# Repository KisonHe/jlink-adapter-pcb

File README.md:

# jlink-adapter-pcb

[bom](http://htmlpreview.github.io/?https://github.com/KisonHe/jlink-adapter-pcb/blob/master/jlink-adapter/bom/ibom.html)

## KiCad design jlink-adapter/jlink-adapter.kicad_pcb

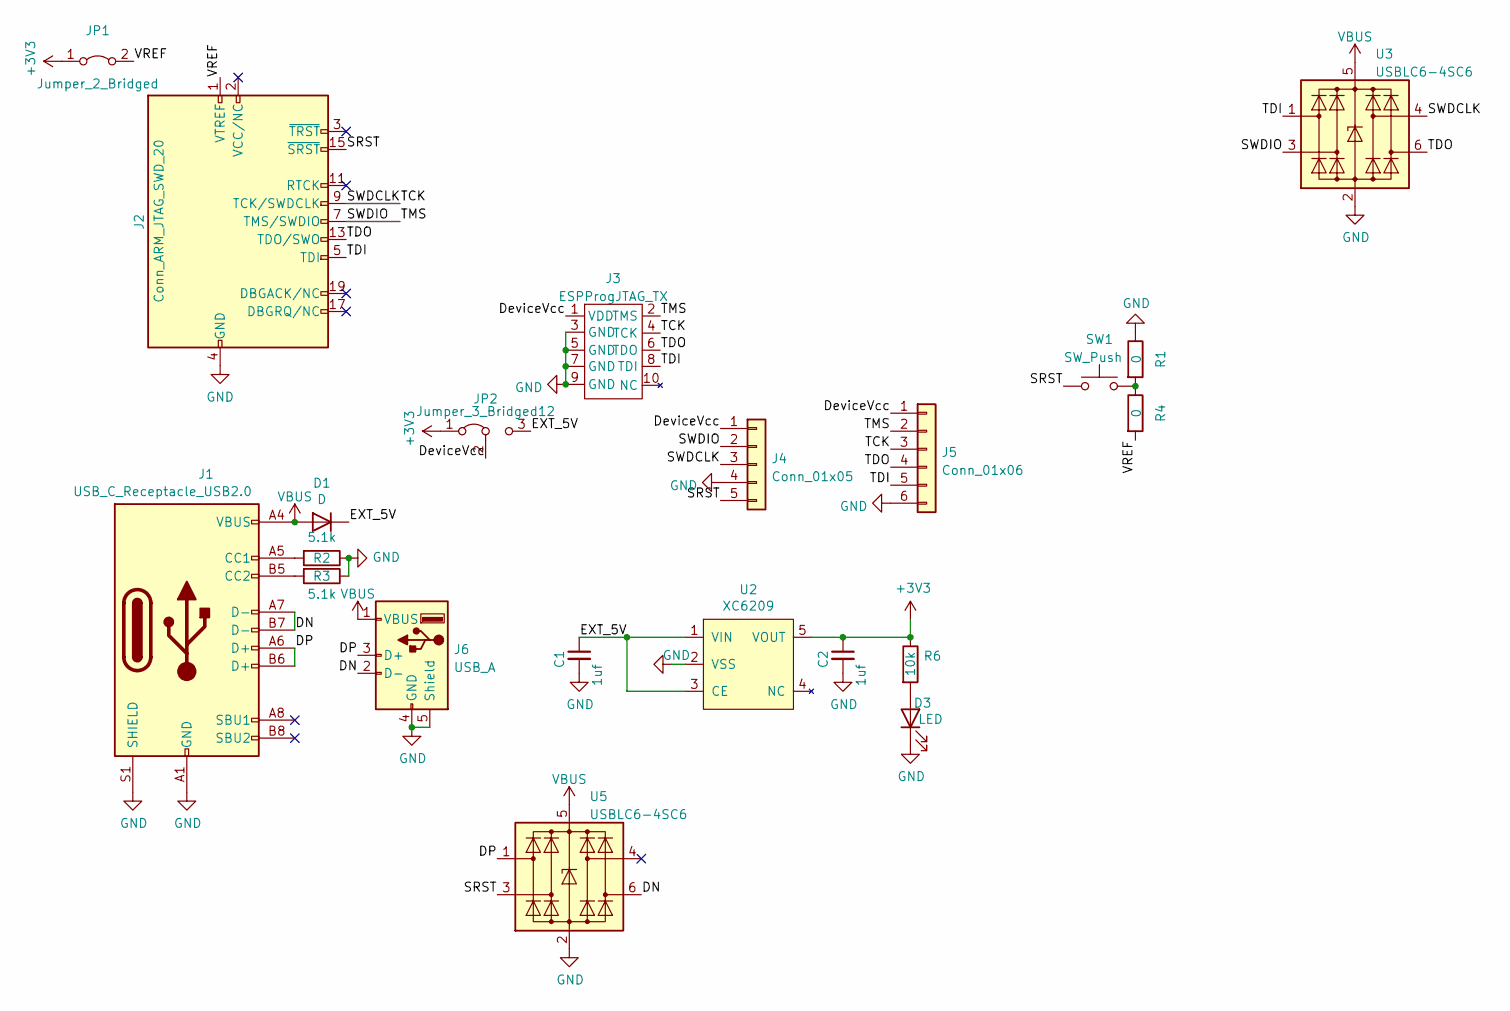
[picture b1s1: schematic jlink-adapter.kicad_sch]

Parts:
C1, C2: 1uf; C_0603_1608Metric
D1: D; C8678; LCSC C8678
D3: LED; LED_0603_1608Metric; LCSC C181863
J1: USB_C_Receptacle_USB2.0; USB_C_Receptacle_HRO_TYPE-C-31-M-12; LCSC C165948
J2: Conn_ARM_JTAG_SWD_20; PinHeader_2x10_P2.54mm_Vertical
J3: ESPProgJTAG_TX; IDC_1.27mm_10P
J4: Conn_01x05; PinHeader_1x05_P2.54mm_Vertical
J5: Conn_01x06; PinHeader_1x06_P2.54mm_Vertical
J6: USB_A; USB_A_CONNFLY_DS1095-WNR0; LCSC C2345
JP1: Jumper_2_Bridged; PinHeader_1x02_P2.54mm_Vertical; LCSC 6209
JP2: Jumper_3_Bridged12; PinHeader_1x03_P2.54mm_Vertical
R1, R4: 0; R_0603_1608Metric; LCSC C325524
R2, R3: 5.1k; R_0603_1608Metric; LCSC C325524
R6: 10k; R_0603_1608Metric
SW1: SW_Push; SW_SPST_CK_RS282G05A3
U2: XC6209; SOT-23-5; LCSC C216624
U3, U5: USBLC6-4SC6; SOT-23-6

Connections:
+3V3: C2.1, JP1.1 (A), JP2.1 (A), R6.1, U2.5 (VOUT)
/DN: J1.A7 (D-), J1.B7 (D-), J6.2 (D-), U5.6 (I/O4)
/DP: J1.A6 (D+), J1.B6 (D+), J6.3 (D+), U5.1 (I/O1)
/DeviceVcc: J3.1 (VDD), J4.1, J5.1, JP2.2 (C)
/EXT_5V: C1.1, D1.1 (K), JP2.3 (B), U2.1 (VIN), U2.3 (CE)
/SRST: J2.15 (~SRST), J4.5, SW1.1, U5.3 (I/O2)
/SWDCLK: J2.9 (TCK/SWDCLK), J3.4 (TCK), J4.3, J5.3, U3.4 (I/O3)
/SWDIO: J2.7 (TMS/SWDIO), J3.2 (TMS), J4.2, J5.2, U3.3 (I/O2)
/TDI: J2.5 (TDI), J3.8 (TDI), J5.5, U3.1 (I/O1)
/TDO: J2.13 (TDO/SWO), J3.6 (TDO), J5.4, U3.6 (I/O4)
/VREF: J2.1 (VTREF), JP1.2 (B), R4.2
GND: C1.2, C2.2, D3.1 (K), J1.A1 (GND), J1.A12 (GND), J1.B1 (GND), J1.B12 (GND), J1.S1 (SHIELD), J2.4 (GND), J2.6 (GND), J2.8 (GND), J2.10 (GND), J2.12 (GND), J2.14 (GND), J2.16 (GND), J2.18 (GND), J2.20 (GND), J3.3 (GND), J3.5 (GND), J3.7 (GND), J3.9 (GND), J4.4, J5.6, J6.4 (GND), J6.5 (Shield), R1.1, R2.1, R3.1, U2.2 (VSS), U3.2 (GND), U5.2 (GND)
unnamed: D3.2 (A), R6.2
unnamed: J1.A5 (CC1), R2.2
unnamed: J1.B5 (CC2), R3.2
unnamed: R1.2, R4.1, SW1.2
VBUS: D1.2 (A), J1.A4 (VBUS), J1.A9 (VBUS), J1.B4 (VBUS), J1.B9 (VBUS), J6.1 (VBUS), U3.5 (VBUS), U5.5 (VBUS)

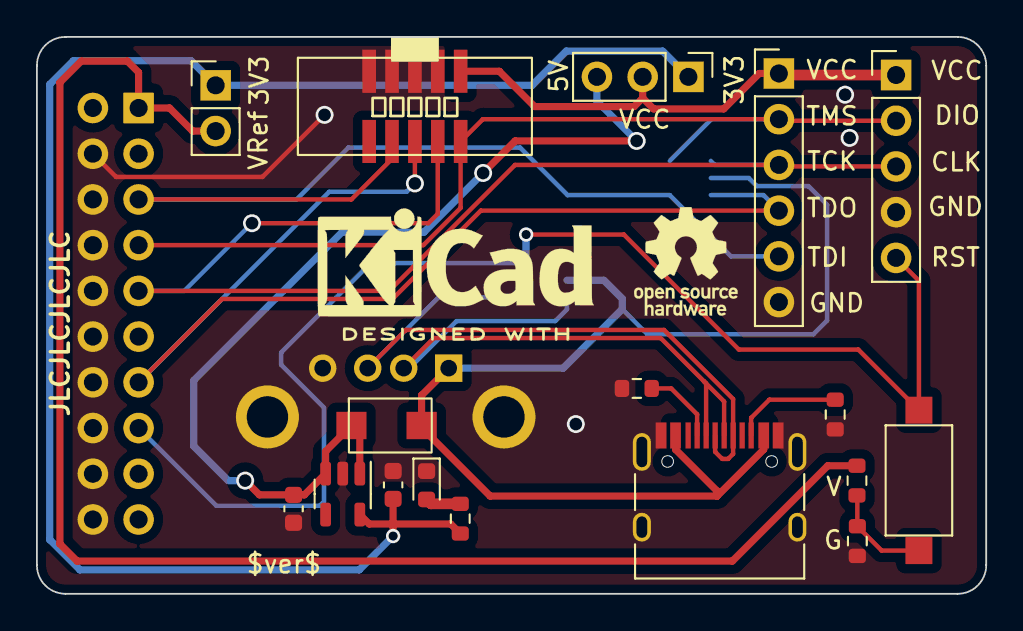
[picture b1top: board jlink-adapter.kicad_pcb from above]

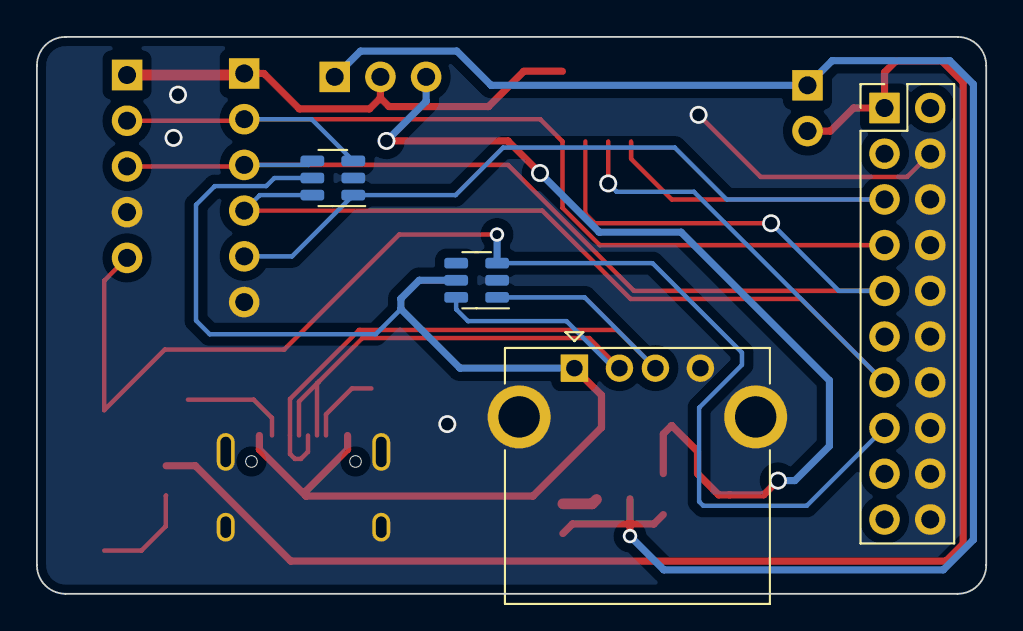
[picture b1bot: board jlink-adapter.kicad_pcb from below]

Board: 2 copper layers, 52.7 x 30.9 mm, 21 parts (4 on the bottom side), 17 nets.

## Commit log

2022-08-11 V0.1
2022-08-12 Change layout
2022-08-12 Add LCSC Number
2022-08-12 Fix URL
2022-08-12 第一次投板
2022-12-14 预备投板
2023-10-18 新kicad
